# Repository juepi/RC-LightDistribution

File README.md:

# RC-Model LED Light Distribution PCB

This small PCB allows you to distribute power for LED lightning in your RC-models. One PCB can handle multiple in- and outputs, through soldering jumpers you are also able to combine in- and outputs. Each output provides through-holes for LED series resistors, 2 outputs can be tied together for a single series resistor for 2 LEDs.  

## Usage
Usage should be fairly clear, you can connect the wires either through the provided through-holes or by using the soldering pads.  

## Production files
Subfolder `gerber` contains files required for production. These files have been prepared for [JLCPCB](https://jlcpcb.com/).  

have fun,  
Juergen

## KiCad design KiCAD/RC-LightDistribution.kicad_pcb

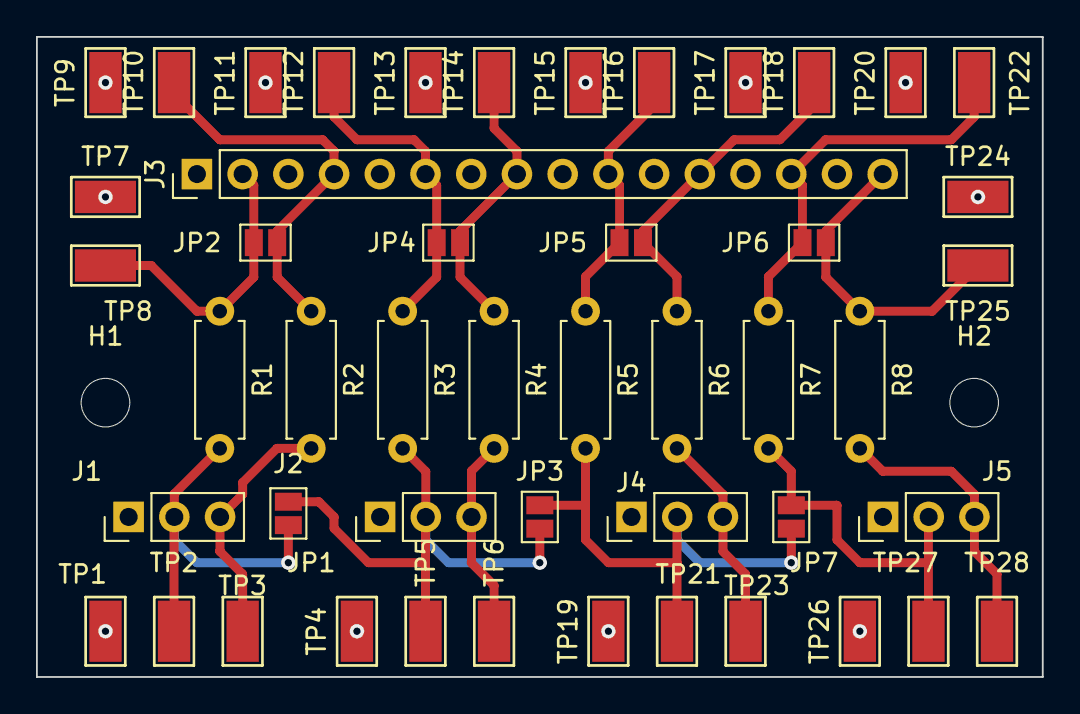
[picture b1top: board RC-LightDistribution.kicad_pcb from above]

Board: 2 copper layers, 55.9 x 35.6 mm, 50 parts (0 on the bottom side), 17 nets.

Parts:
H1, H2: MountingHole_2.7mm_M2.5
J1, J2, J4, J5: PinHeader_1x03_P2.54mm_Vertical
J3: PinHeader_1x16_P2.54mm_Vertical
JP1, JP2, JP3, JP4, JP5, JP6, JP7: SolderJumper-2_P1.3mm_Open_Pad1.0x1.5mm
R1, R2, R3, R4, R5, R6, R7, R8: R_Axial_DIN0207_L6.3mm_D2.5mm_P7.62mm_Horizontal
TP1, TP2, TP3, TP4, TP5, TP6, TP7, TP8, TP9, TP10, TP11, TP12, TP13, TP14, TP15, TP16, TP17, TP18, TP19, TP20, TP21, TP22, TP23, TP24, TP25, TP26, TP27, TP28: TestPoint_Keystone_5015_Micro-Minature

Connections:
unnamed: J1.3, R2.2, TP3.1
unnamed: J2.2, JP1.1 (A), JP3.2 (B), R3.2, TP5.1
unnamed: J2.3, R4.2, TP6.1
unnamed: J3.2, JP2.1 (A), R1.1, TP8.1
unnamed: J3.4, JP2.2 (B), R2.1, TP10.1
unnamed: J3.6, JP4.1 (A), R3.1, TP12.1
unnamed: J3.8, JP4.2 (B), R4.1, TP14.1
unnamed: J3.10, JP5.1 (A), R5.1, TP16.1
unnamed: J3.12, JP5.2 (B), R6.1, TP18.1
unnamed: J3.14, JP6.1 (A), R7.1, TP22.1
unnamed: J3.16, JP6.2 (B), R8.1, TP25.1
unnamed: J4.2, JP3.1 (A), JP7.2 (B), R5.2, TP21.1
unnamed: J4.3, R6.2, TP23.1
unnamed: J5.2, JP7.1 (A), R7.2, TP27.1
unnamed: J5.3, R8.2, TP28.1
unnamed: J1.2, JP1.2 (B), R1.2, TP2.1
VCC: J1.1, J2.1, J3.1, J3.3, J3.5, J3.7, J3.9, J3.11, J3.13, J3.15, J4.1, J5.1, TP1.1, TP4.1, TP7.1, TP9.1, TP11.1, TP13.1, TP15.1, TP17.1, TP19.1, TP20.1, TP24.1, TP26.1
